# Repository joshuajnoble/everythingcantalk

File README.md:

# everythingcantalk
Workshop for Resonate 2015

This is the boards, libraries, and information for the everythingcantalk workshop being held at [Resonate 2015](http://resonate.io/2015/)

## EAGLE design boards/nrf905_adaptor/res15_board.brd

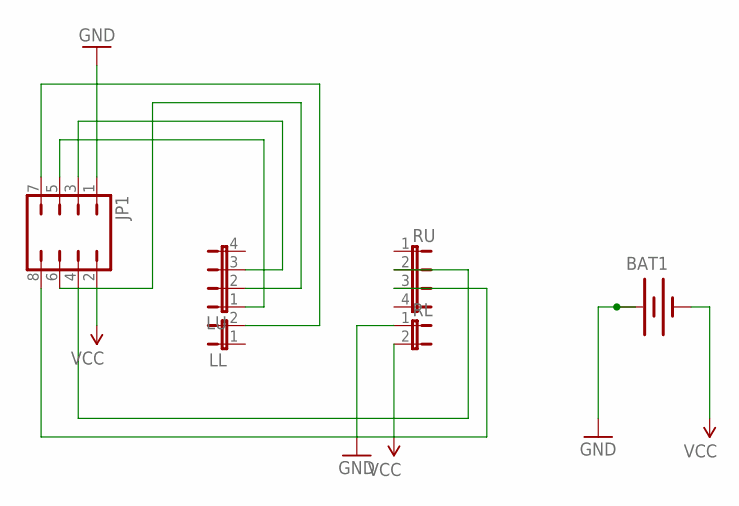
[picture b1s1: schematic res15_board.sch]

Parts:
BAT1: BATTERY245MM; BATTCON_245MM
JP1: JP4Q
LL: JP1E; JP1
LU: JP4E; JP4
RL: JP1E; JP1
RU: JP4E; JP4

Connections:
GND: BAT1.1 (+), JP1.1, RL.1
unnamed: JP1.5, LU.1
unnamed: JP1.3, LU.3
unnamed: JP1.4, RU.2
unnamed: JP1.6, LU.2
unnamed: JP1.7, LL.2
unnamed: JP1.8, RU.3
VCC: BAT1.2 (-), JP1.2, RL.2

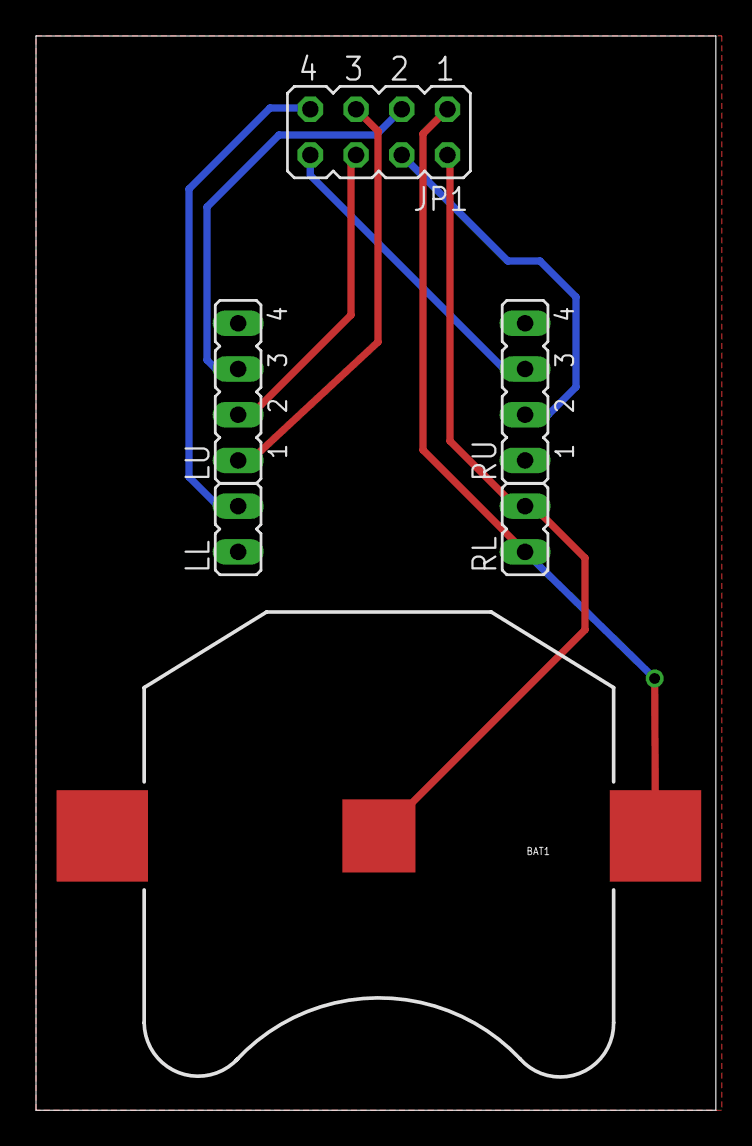
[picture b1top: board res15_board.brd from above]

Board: 2 copper layers, 37.8 x 59.7 mm, 6 parts (0 on the bottom side), 8 nets.

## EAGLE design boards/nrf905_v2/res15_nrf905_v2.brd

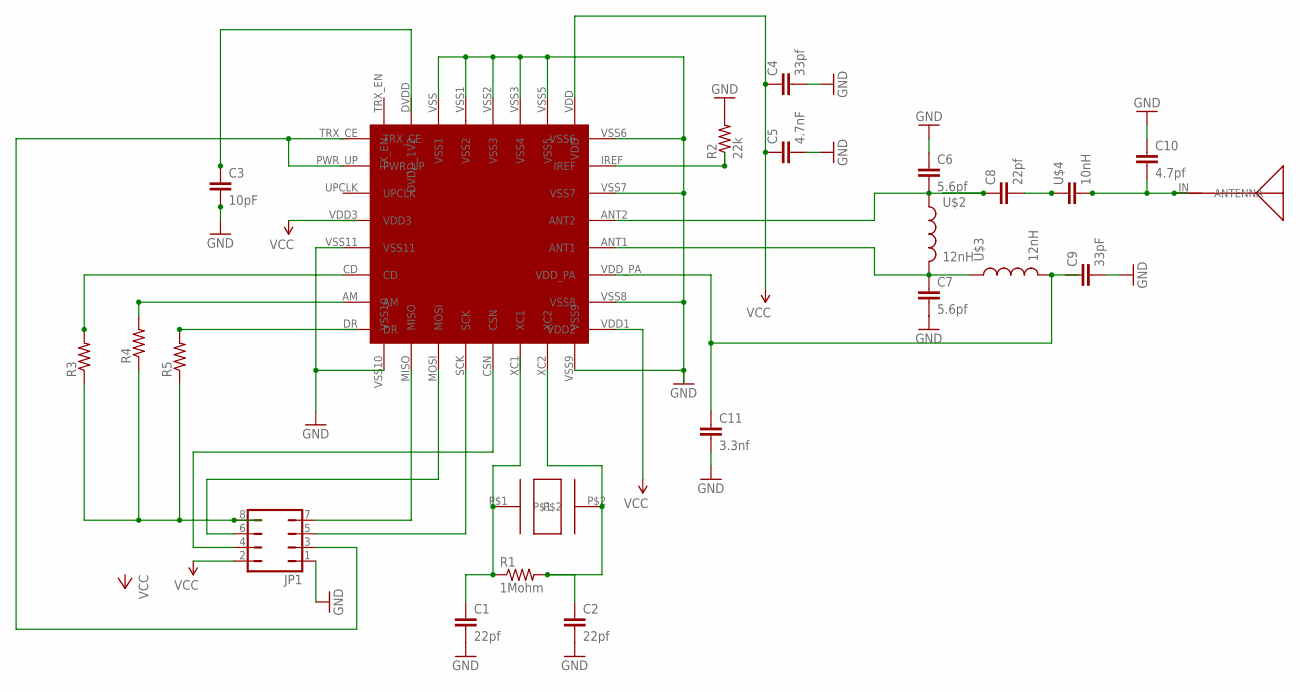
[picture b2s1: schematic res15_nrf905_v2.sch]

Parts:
C1, C2, C8: 22pf; 0603-CAP
C3: 10pF; 0603-CAP
C4: 33pf; 0603-CAP
C5: 4.7nF; 0603-CAP
C6, C7: 5.6pf; 0603-CAP
C9: 33pF; 0603-CAP
C10: 4.7pf; 0603-CAP
C11: 3.3nf; 0603-CAP
JP1: JP4Q
R1: 1Mohm; 0603-RES
R2: 22k; 0603-RES
R3, R4, R5: RESISTOR0603-RES; 0603-RES
U$1: NRF905
U$2, U$3: 12nH; 0603
U$4: 10nH; 0603-CAP
U$5: WURTH-7488910092
U$6: HC46X

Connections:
DR: U$1.DR
GND: C1.2, C2.2, C3.2, C4.2, C5.2, C6.1, C7.2, C9.2, C10.1, C11.2, JP1.1, R2.2, U$1.VSS (VSS1), U$1.VSS1 (VSS2), U$1.VSS2 (VSS3), U$1.VSS3 (VSS4), U$1.VSS5, U$1.VSS6, U$1.VSS7, U$1.VSS8, U$1.VSS9, U$1.VSS10, U$1.VSS11
unnamed: C1.1, R1.1, U$6.P$1
unnamed: C2.1, R1.2, U$1.XC2, U$6.P$2
unnamed: C7.1, U$1.ANT1, U$2.2, U$3.1
unnamed: JP1.7, U$1.MISO
unnamed: JP1.6, U$1.MOSI
unnamed: JP1.5, U$1.SCK
unnamed: C11.1, U$1.VDD_PA, U$3.2
unnamed: C6.2, C8.1, U$1.ANT2, U$2.1
unnamed: C8.2, U$4.1
unnamed: C10.2, U$4.2, U$5.IN
unnamed: JP1.4, U$1.CSN
unnamed: R2.1, U$1.IREF
unnamed: JP1.3, U$1.PWR_UP, U$1.TRX_CE
unnamed: R3.2, U$1.CD
unnamed: JP1.8, R3.1, R4.1, R5.1
unnamed: R4.2, U$1.AM
VCC: C4.1, C5.1, JP1.2, U$1.VDD, U$1.VDD1 (VDD2)
VDD3: U$1.VDD3

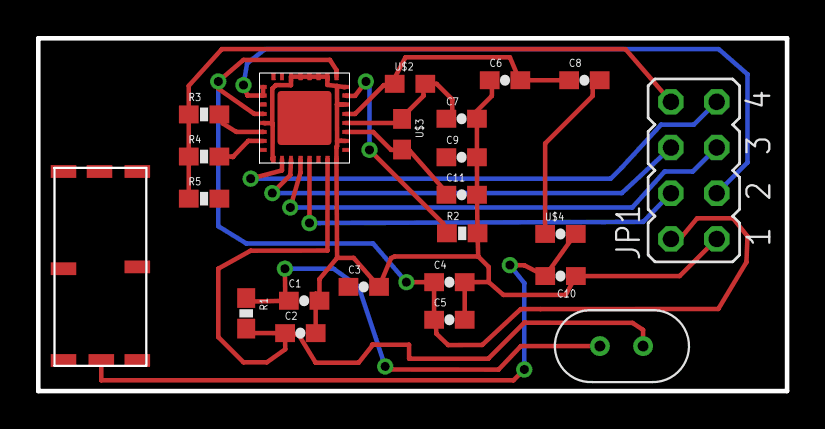
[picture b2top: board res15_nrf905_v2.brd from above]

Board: 2 copper layers, 41.6 x 19.6 mm, 23 parts (0 on the bottom side), 18 nets.

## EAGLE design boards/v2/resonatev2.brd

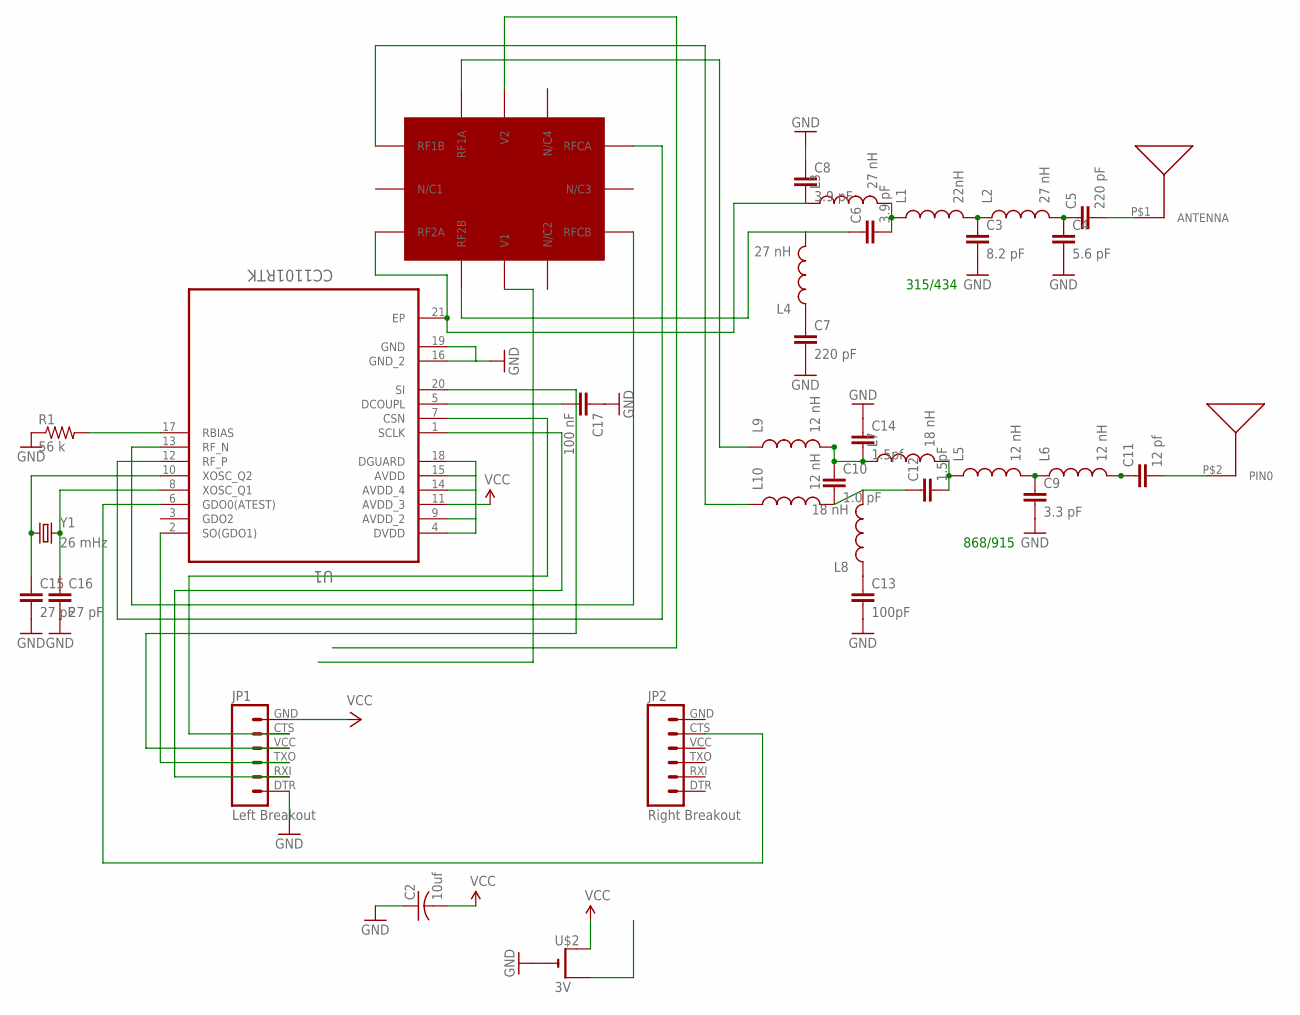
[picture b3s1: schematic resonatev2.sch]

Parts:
C2: 10uf; C0603
C3: 8.2 pF; 0402-CAP
C4: 5.6 pF; 0402-CAP
C5, C7: 220 pF; 0402-CAP
C6, C8: 3.9 pF; 0402-CAP
C9: 3.3 pF; 0402-CAP
C10: 1.0 pF; 0402-CAP
C11: 12 pf; 0402-CAP
C12: 1.5pF; 0402-CAP
C13: 100pF; 0402-CAP
C14: 1.5pf; 0402-CAP
C15, C16: 27 pF; 0402-CAP
C17: 100 nF; 0402-CAP
JP1: Left Breakout; 1X06
JP2: Right Breakout; 1X06
L1: 22nH; C0402
L2, L3, L4: 27 nH; C0402
L5, L6, L9, L10: 12 nH; C0402
L7, L8: 18 nH; C0402
R1: 56 k; 0603-RES
U1: CC1101RTK; QFN50P400X400X90-21N
U$2: 3V; CR2032-THRU
U$3: ANT-868-JJB-ST
U$5: SKY13354-368LF
U$6: ANT1204F002R0433A
Y1: 26 mHz; CRYSTAL-SMD-5X3

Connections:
GND: C2.1, C3.2, C4.2, C7.2, C8.1, C9.2, C13.2, C14.1, C15.2, C16.2, C17.1, JP1.DTR (1), R1.1, U1.16 (GND_2), U1.19 (GND), U$2.-
unnamed: JP1.TXO (3), U1.2 (SO(GDO1))
unnamed: JP2.CTS (5), U1.6 (GDO0(ATEST))
unnamed: C3.1, L1.2, L2.1
unnamed: C4.1, C5.1, L2.2
unnamed: C6.1, L4.2, U$5.RF2B
unnamed: C7.1, L4.1
unnamed: C8.2, L3.1, U1.21 (EP), U$5.RF2A
unnamed: C9.1, L5.2, L6.1
unnamed: C6.2, L1.1, L3.2
unnamed: C11.1, L6.2
unnamed: C10.2, C12.1, L8.2, L10.2
unnamed: C13.1, L8.1
unnamed: C10.1, C14.2, L7.1, L9.2
unnamed: C12.2, L5.1, L7.2
unnamed: C5.2, U$6.P$1
unnamed: C11.2, U$3.P$2
unnamed: U1.12 (RF_P), U$5.RFCA
unnamed: U1.13 (RF_N), U$5.RFCB
unnamed: C15.1, U1.10 (XOSC_Q2), Y1.1
unnamed: L9.1, U$5.RF1A
unnamed: L10.1, U$5.RF1B
unnamed: C16.1, U1.8 (XOSC_Q1), Y1.3 (2)
unnamed: R1.2, U1.17 (RBIAS)
unnamed: JP1.VCC (4), U1.20 (SI)
unnamed: C17.2, U1.5 (DCOUPL)
P2: U$5.V1
P3: U$5.V2
P4: JP1.RXI (2), U1.1 (SCLK)
P6: JP1.CTS (5), U1.7 (CSN)
VCC: C2.2, JP1.GND (6), U1.4 (DVDD), U1.9 (AVDD_2), U1.11 (AVDD_3), U1.14 (AVDD_4), U1.15 (AVDD), U1.18 (DGUARD), U$2.+1 (+)

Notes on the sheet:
315/434
868/915

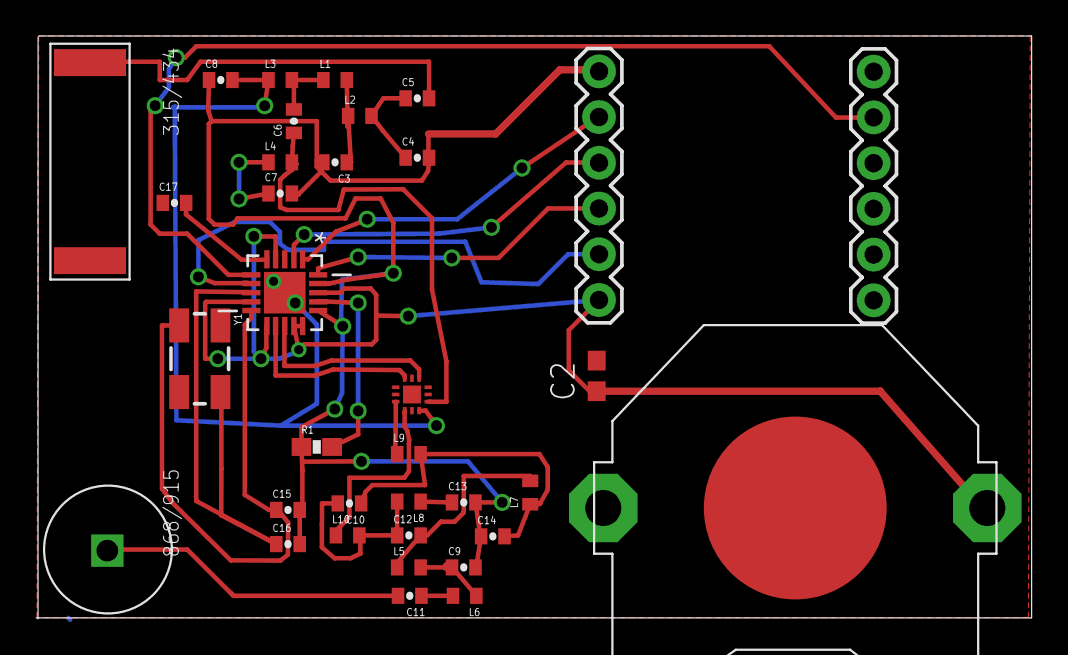
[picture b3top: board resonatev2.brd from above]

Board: 2 copper layers, 55.3 x 32.4 mm, 35 parts (0 on the bottom side), 29 nets.

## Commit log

2015-01-21 correct version
2015-01-21 updating post-merge
2015-01-22 adding boards
2015-01-22 moving boards
2015-01-22 adding mask
2015-01-24 updating solder mask
2015-02-15 reorganziing
2015-02-15 making a new board
2015-02-25 adding new boards for nrf905
2015-03-14 adding more boards
2015-03-24 adding code for BleNANO to nrf24l01

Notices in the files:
parts and their libraries:
SparkFun: Licensing: CC v3.0 Share-Alike You are welcome to use this library for commercial purposes.
SparkFun-Connectors: Licensing: Creative Commons ShareAlike 4.0 International - https://creativecommons.org/licenses/by-sa/4.0
